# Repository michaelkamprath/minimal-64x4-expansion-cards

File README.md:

# Expansion Cards for Minimal 64x4 Computer
This repository contains various expansion cards for the [Minimal 64x4 Home Computer](https://github.com/slu4coder/Minimal-64x4-Home-Computer/) design by Carsten Herting, known as [slu4 on YouTube](https://www.youtube.com/channel/UCXYQcMpUBT3aaQKfmAVJNow).

## Back Plane
The [back plane provided in this repository](./expansion-backplane/) allows for more than one expansion card to be connected to the Minimal 64x4. It also provides a more convenient barrel jack power connector with a on/off switch to power the Minimal 64x4.

## Cards

* [**Speech Synthesizer**](./speech-synthesizer/) - This board provides support for interfacing with a TMS5220C speech synthesizer. 
* [**Multiplier Card**](./multiplier/) - This board provides a hardware implimentation of 8-bit integer multiplications, significantly improving the speed of multiplications over software-implementations.
* [**Timer**](./timer/) - Counts the cycles of the Minimal 64x4's system clock to enable precision timing of events.

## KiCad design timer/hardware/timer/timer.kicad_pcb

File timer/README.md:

# Timer - Clock Counter
This Timer card provides a convenient way to capture precise timing on the Minimal 64x4 by counting clock cycles. The counter is resettable to 0, allowing specific operations to be timed. The counter is 48 bits wide, which allows time ranges up to about 1.1 years at the Minimal 64x4's 8 MHz clock frequency.

## Hardware Design
[This card](./hardware/) uses six 74HC590 8-bit counters arranged in a cascading carry chain to create a 48-bit counter. The 74HC590 has tri-state outputs, so each counter IC is connected directly to the data bus and remains in high-Z unless selected to drive its latched value. Card control is handled by two 74HC688 comparators (address decode) and an ATF22V10C programmable logic device (control logic for read byte select, latch, and reset). The combinational logic is captured in [the PLD code](./pld-files/).

## Memory Map

Define:

`base = $FE00 + (x << 4) + y`

Where:
- `y` is controlled by jumper `J1` (address bit A3): `J1` open => `y = 0`, `J1` bridged => `y = 8`.
- `x` is controlled by jumpers `J2`-`J5` (address bits A4-A7): `J2` is A4 (LSB of `x`) and `J5` is A7 (MSB of `x`).
- Jumpers are named from the PCB silkscreen (`J1`-`J5`).

| Offset From `base` | R/W   | Function       | Description |
| ------------------ | ----- | -------------- | ----------- |
| `+0`               | Read  | Latched Byte 0 | Read latched counter value, byte 0 (LSB) |
| `+1`               | Read  | Latched Byte 1 | Read latched counter value, byte 1 |
| `+2`               | Read  | Latched Byte 2 | Read latched counter value, byte 2 |
| `+3`               | Read  | Latched Byte 3 | Read latched counter value, byte 3 |
| `+4`               | Read  | Latched Byte 4 | Read latched counter value, byte 4 |
| `+5`               | Read  | Latched Byte 5 | Read latched counter value, byte 5 (MSB) |
| `+6`               | Write | Latch Counter  | Latch (snapshot) the current 48-bit counter into the output registers. Any value may be written to trigger this action. |
| `+7`               | Write | Reset Counter  | Reset the counter value to `0`. Any value may be written to trigger this action. |

Concrete ranges for a selected `x`:
- `J1` open (`y = 0`): registers are at `$FEx0`-`$FEx7`.
- `J1` bridged (`y = 8`): registers are at `$FEx8`-`$FExF`.

Notes:
- Bridging all jumpers `J2` through `J5` sets `x` to `$F`; leaving them open sets `x` to `$0` (default).
- Reading `$FEx0`-`$FEx5` (or `$FEx8`-`$FExD` when `J1` is bridged) returns the last value latched by writing to the latch register, not necessarily the current counter value.
- Resetting the counter does not latch a `0` value.

### Default Jumper Setttings
The code in this repo assumes the timer card's base address is $FE28. This is accomplished by jumpering J1 and J3, and leaving the others open.

## Time Range
This card has a 48-bit counter that is read one byte at a time. Not all bytes need to be read, but reading fewer bytes reduces the effective time range captured. At the **Minimal 64x4**'s 8 MHz clock, the maximum time range by number of bytes read is shown in this table:

| Bytes | Bits | Max Seconds (s) | Approx Time                      |
| ----: | ---: | --------------: | -------------------------------- |
|     6 |   48 | 35184372.088832 | 407.22652996 days (~1.115 years) |
|     5 |   40 |   137438.953472 | 38.17748708 hours (~1.5907 days) |
|     4 |   32 |      536.870912 | 8.94784853 minutes               |
|     3 |   24 |        2.097152 | 2.097152 seconds                 |
|     2 |   16 |        0.008192 | 8.192 ms                         |
|     1 |    8 |        0.000032 | 32 µs                            |

The latched bytes are arranged in little-endian order: `base + 0` is the LSB and `base + 5` is the MSB.

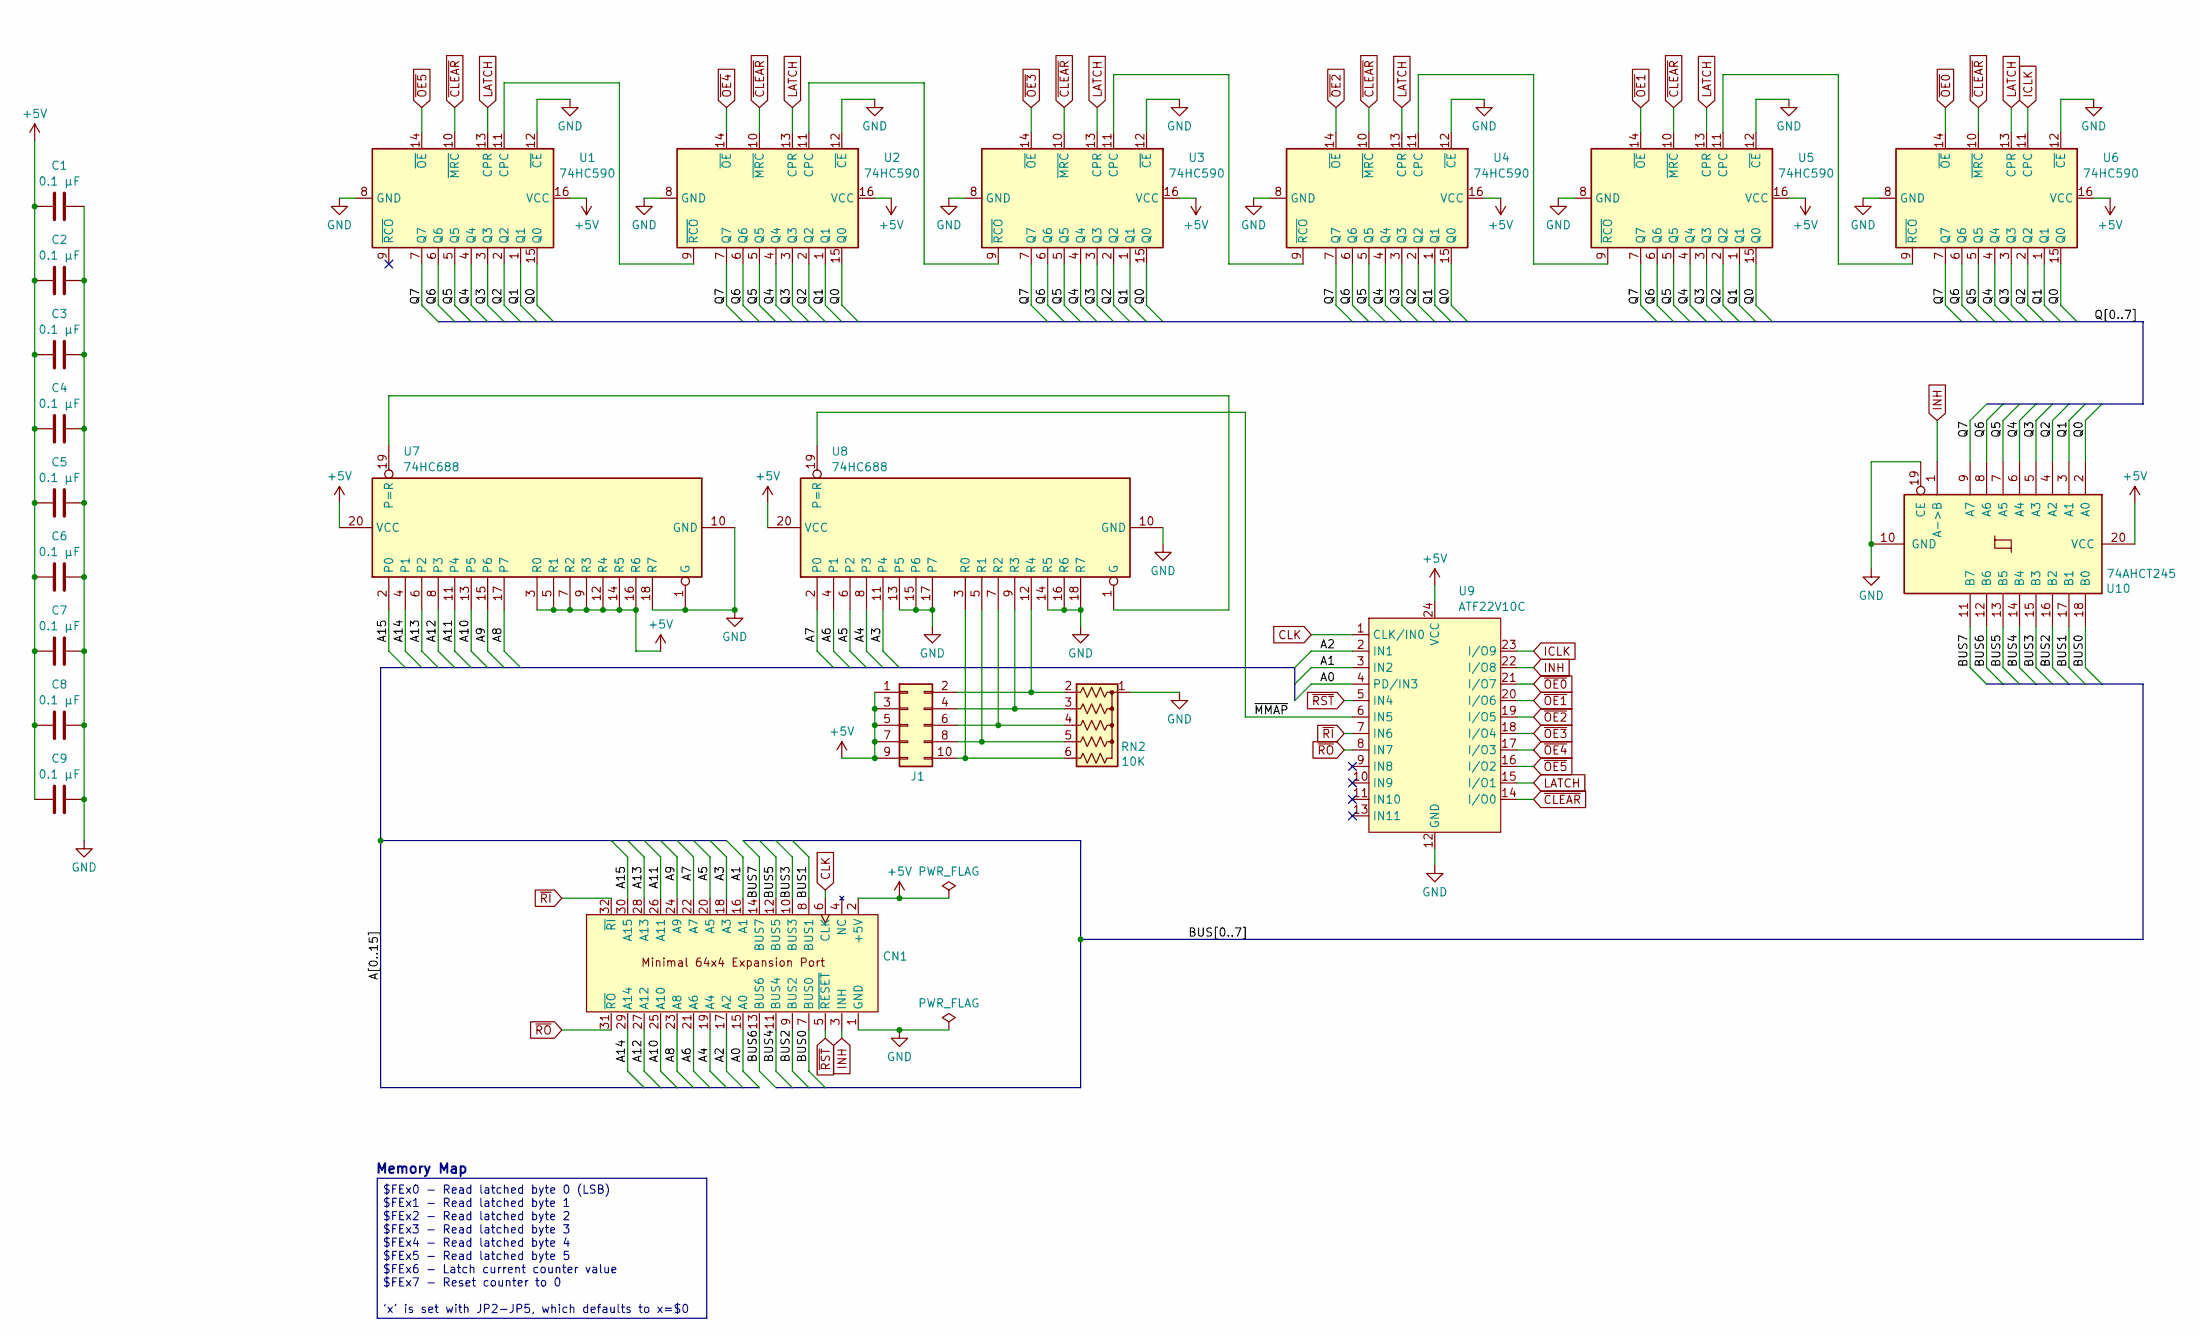
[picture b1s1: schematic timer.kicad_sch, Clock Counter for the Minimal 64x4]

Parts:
C1, C2, C3, C4, C5, C6, C7, C8, C9: 0.1 µF; C_Disc_D3.4mm_W2.1mm_P2.50mm
CN1: PinHeader_2x16_P2.54mm_Horizontal
J1: Conn_02x05_Odd_Even; PinHeader_2x05_P2.54mm_Vertical
RN2: 10K; R_Array_SIP6
U1, U2, U3, U4, U5, U6: 74HC590; DIP-16_W7.62mm_Socket
U7, U8: 74HC688; DIP-20_W7.62mm_Socket
U9: ATF22V10C; DIP-24_W7.62mm_Socket
U10: 74AHCT245; DIP-20_W7.62mm_Socket

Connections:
+5V: C1.1, C2.1, C3.1, C4.1, C5.1, C6.1, C7.1, C8.1, C9.1, CN1.2 (+5V), J1.1, J1.3, J1.5, J1.7, J1.9, U1.16 (VCC), U2.16 (VCC), U3.16 (VCC), U4.16 (VCC), U5.16 (VCC), U6.16 (VCC), U7.3 (R0), U7.5 (R1), U7.7 (R2), U7.9 (R3), U7.12 (R4), U7.14 (R5), U7.16 (R6), U7.20 (VCC), U8.20 (VCC), U9.24 (VCC), U10.20 (VCC)
/A0: CN1.15 (A0), U9.4 (PD/IN3)
/A1: CN1.16 (A1), U9.3 (IN2)
/A2: CN1.17 (A2), U9.2 (IN1)
/A3: CN1.18 (A3), U8.11 (P4)
/A4: CN1.19 (A4), U8.8 (P3)
/A5: CN1.20 (A5), U8.6 (P2)
/A6: CN1.21 (A6), U8.4 (P1)
/A7: CN1.22 (A7), U8.2 (P0)
/A8: CN1.23 (A8), U7.17 (P7)
/A9: CN1.24 (A9), U7.15 (P6)
/A10: CN1.25 (A10), U7.13 (P5)
/A11: CN1.26 (A11), U7.11 (P4)
/A12: CN1.27 (A12), U7.8 (P3)
/A13: CN1.28 (A13), U7.6 (P2)
/A14: CN1.29 (A14), U7.4 (P1)
/A15: CN1.30 (A15), U7.2 (P0)
/BUS0: CN1.7 (BUS0), U10.18 (B0)
/BUS1: CN1.8 (BUS1), U10.17 (B1)
/BUS2: CN1.9 (BUS2), U10.16 (B2)
/BUS3: CN1.10 (BUS3), U10.15 (B3)
/BUS4: CN1.11 (BUS4), U10.14 (B4)
/BUS5: CN1.12 (BUS5), U10.13 (B5)
/BUS6: CN1.13 (BUS6), U10.12 (B6)
/BUS7: CN1.14 (BUS7), U10.11 (B7)
/Q0: U1.15 (Q0), U2.15 (Q0), U3.15 (Q0), U4.15 (Q0), U5.15 (Q0), U6.15 (Q0), U10.2 (A0)
/Q1: U1.1 (Q1), U2.1 (Q1), U3.1 (Q1), U4.1 (Q1), U5.1 (Q1), U6.1 (Q1), U10.3 (A1)
/Q2: U1.2 (Q2), U2.2 (Q2), U3.2 (Q2), U4.2 (Q2), U5.2 (Q2), U6.2 (Q2), U10.4 (A2)
/Q3: U1.3 (Q3), U2.3 (Q3), U3.3 (Q3), U4.3 (Q3), U5.3 (Q3), U6.3 (Q3), U10.5 (A3)
/Q4: U1.4 (Q4), U2.4 (Q4), U3.4 (Q4), U4.4 (Q4), U5.4 (Q4), U6.4 (Q4), U10.6 (A4)
/Q5: U1.5 (Q5), U2.5 (Q5), U3.5 (Q5), U4.5 (Q5), U5.5 (Q5), U6.5 (Q5), U10.7 (A5)
/Q6: U1.6 (Q6), U2.6 (Q6), U3.6 (Q6), U4.6 (Q6), U5.6 (Q6), U6.6 (Q6), U10.8 (A6)
/Q7: U1.7 (Q7), U2.7 (Q7), U3.7 (Q7), U4.7 (Q7), U5.7 (Q7), U6.7 (Q7), U10.9 (A7)
/~MMAP: U8.19 (P=R), U9.6 (IN5)
CLK: CN1.6 (CLK), U9.1 (CLK/IN0)
GND: C1.2, C2.2, C3.2, C4.2, C5.2, C6.2, C7.2, C8.2, C9.2, CN1.1 (GND), RN2.1 (common), U1.8 (GND), U1.12 (~CE), U2.8 (GND), U2.12 (~CE), U3.8 (GND), U3.12 (~CE), U4.8 (GND), U4.12 (~CE), U5.8 (GND), U5.12 (~CE), U6.8 (GND), U6.12 (~CE), U7.1 (G), U7.10 (GND), U7.18 (R7), U8.10 (GND), U8.13 (P5), U8.14 (R5), U8.15 (P6), U8.16 (R6), U8.17 (P7), U8.18 (R7), U9.12 (GND), U10.10 (GND), U10.19 (CE)
ICLK: U6.11 (CPC), U9.23 (I/O9)
INH: CN1.3 (INH), U9.22 (I/O8), U10.1 (A->B)
LATCH: U1.13 (CPR), U2.13 (CPR), U3.13 (CPR), U4.13 (CPR), U5.13 (CPR), U6.13 (CPR), U9.15 (I/O1)
unnamed: J1.2, RN2.2 (R1), U8.12 (R4)
unnamed: J1.4, RN2.3 (R2), U8.9 (R3)
unnamed: J1.6, RN2.4 (R3), U8.7 (R2)
unnamed: J1.8, RN2.5 (R4), U8.5 (R1)
unnamed: J1.10, RN2.6 (R5), U8.3 (R0)
unnamed: U1.11 (CPC), U2.9 (~RCO)
unnamed: U2.11 (CPC), U3.9 (~RCO)
unnamed: U3.11 (CPC), U4.9 (~RCO)
unnamed: U4.11 (CPC), U5.9 (~RCO)
unnamed: U5.11 (CPC), U6.9 (~RCO)
unnamed: U7.19 (P=R), U8.1 (G)
~CLEAR: U1.10 (~MRC), U2.10 (~MRC), U3.10 (~MRC), U4.10 (~MRC), U5.10 (~MRC), U6.10 (~MRC), U9.14 (I/O0)
~OE0: U6.14 (~OE), U9.21 (I/O7)
~OE1: U5.14 (~OE), U9.20 (I/O6)
~OE2: U4.14 (~OE), U9.19 (I/O5)
~OE3: U3.14 (~OE), U9.18 (I/O4)
~OE4: U2.14 (~OE), U9.17 (I/O3)
~OE5: U1.14 (~OE), U9.16 (I/O2)
~RI: CN1.32 (~RI), U9.7 (IN6)
~RO: CN1.31 (~RO), U9.8 (IN7)
~RST: CN1.5 (~RESET), U9.5 (IN4)

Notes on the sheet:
$FEx0 - Read latched byte 0 (LSB) $FEx1 - Read latched byte 1 $FEx2 - Read latched byte 2 $FEx3 - Read latched byte 3 $FEx4 - Read latched byte 4 $FEx5 - Read latched byte 5 $FEx6 - Latch current counter value $FEx7 - Reset counter to 0 'x' is set with JP2-JP5, which defaults to x=$0
Memory Map

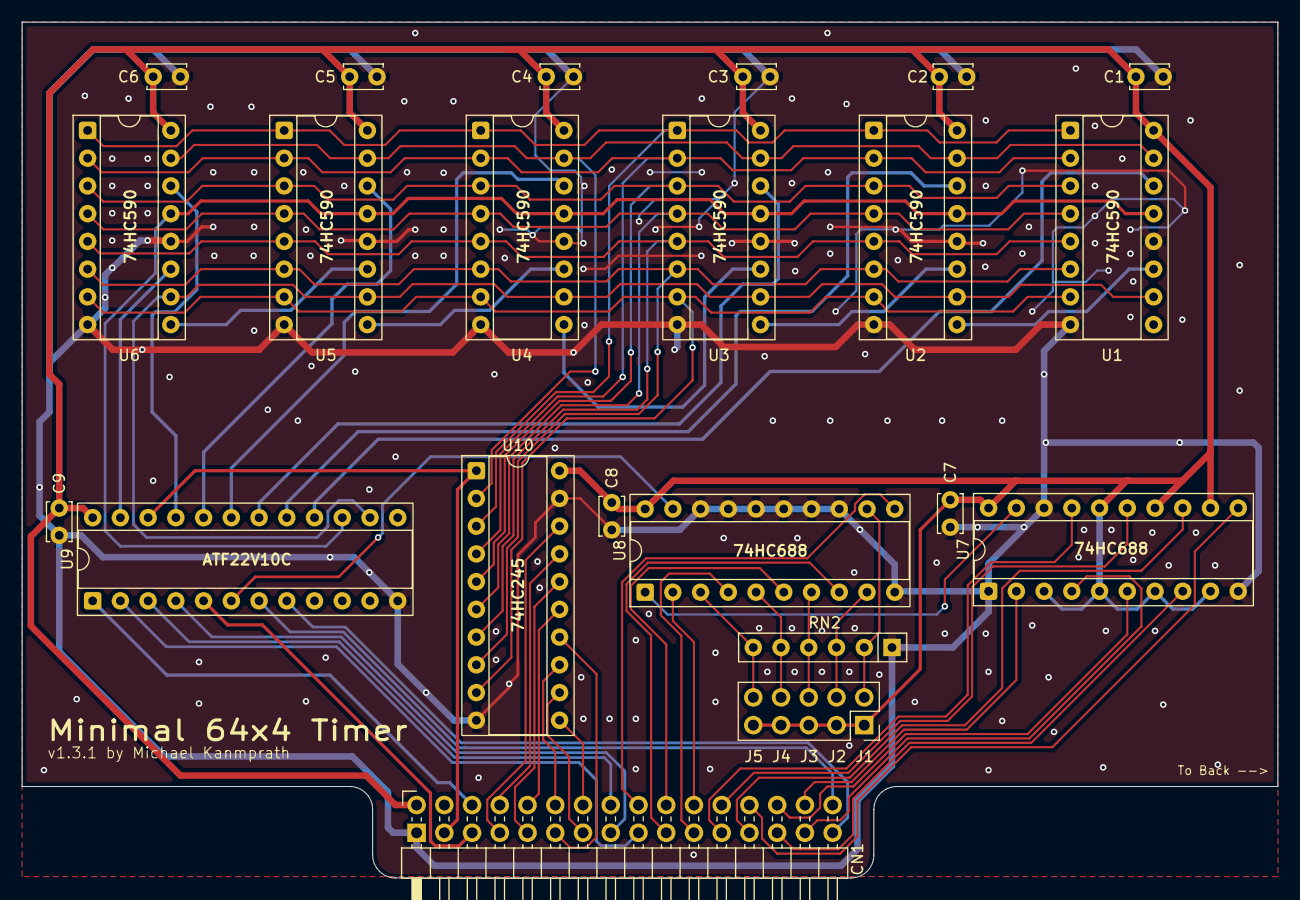
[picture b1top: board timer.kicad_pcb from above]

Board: 2 copper layers, 115.0 x 78.4 mm, 22 parts (0 on the bottom side), 60 nets.

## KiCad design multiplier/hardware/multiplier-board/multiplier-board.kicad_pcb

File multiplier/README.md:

# Integer Multiplication Accelerator for the Minimal 64x4 Computer
This project enables hardware-accelerated multiplication on the [Minimal 64x4 Home Computer](https://github.com/slu4coder/Minimal-64x4-Home-Computer/), exploring how multiplication works at a fundamental level in both software and hardware, using the Minimal 64x4 homebrew computer as a real-world test platform. Starting with a classic shifted-add multiplication algorithm implemented entirely in assembly, the project demonstrates both the mechanics and performance limits of software-based multiplication on an 8-bit CPU.

To dramatically improve performance, a dedicated hardware multiplier card is designed and built using discrete 74-series logic. The board implements a fully combinational 8-bit × 8-bit multiplier with memory-mapped I/O, allowing the CPU to offload multiplication and receive a 16-bit result in just a few clock cycles. The design is then extended in software to support full 16-bit × 16-bit multiplication through careful carry management.

The impact of hardware acceleration is demonstrated using a Mandelbrot renderer, where thousands of multiplications per frame make performance differences immediately visible. By comparing software-only and hardware-accelerated runs on real hardware, the project shows how a simple, purpose-built coprocessor can transform computational performance on a retro-style system.

# Hardware Multiplier Design
The hardware multiplier is a memory-mapped expansion board for the Minimal 64x4 that implements an 8-bit × 8-bit unsigned multiplication entirely in combinational logic. The design uses a planar array of 74AHCT08 AND gates to generate all partial products, followed by a cascade of 74HCT283 4-bit adders to sum those partial products and propagate carries. Because the multiplier core is purely combinational, no clocking, state machine, or control logic is required; once valid operands are presented, the result settles after the inherent gate propagation delay.

Operands are latched from the system data bus using 74AHCT374 registers to isolate the combinational logic from the shared bus and to ensure stable inputs during computation. The 16-bit result is continuously driven internally and presented to the host system through 74AHCT245 bidirectional bus transceivers when the board is selected. Address decoding is handled using 74HCT688 magnitude comparators, with a small programmable logic device (ATF16V8) providing glue logic for timing, output enable control, and bus arbitration.

Worst-case propagation delay is dominated by carry propagation through the adder array and is approximately 160 ns, corresponding to roughly two CPU cycles on an 8 MHz Minimal 64x4. From the CPU’s perspective, multiplication is reduced to a small number of memory writes and reads, enabling a substantial performance improvement over the software-only shifted-add implementation.

```text
                     ┌─────────────────────────┐
                     │        CPU / BUS        │
                     │  Address • Data • Ctrl  │
                     └───────────┬─────────────┘
                                 │
                        Memory-Mapped I/O
                                 │
        ┌────────────────────────▼────────────────────────┐
        │            Hardware Multiplier Board            │
        │                                                 │
        │  ┌───────────────┐      ┌────────────────────┐  │
        │  │ Input Latch A │◄─────┤                    │  │
        │  │  (8-bit)      │      │                    │  │
        │  └───────────────┘      │                    │  │
        │                         │                    │  │
        │  ┌───────────────┐      │  Combinational     │  │
        │  │ Input Latch B │◄─────┤  Multiplier Core   │  │
        │  │  (8-bit)      │      │  (AND Plane +      │  │
        │  └───────────────┘      │   Adder Array)     │  │
        │                         │                    │  │
        │                         │                    │  │
        │                         └─────────┬──────────┘  │
        │                                   │             │
        │                          16-bit Result          │
        │                                   │             │
        │                    ┌──────────────▼────────────┐│
        │                    │  Output Bus Transceivers  ││
        │                    │       (16-bit)            ││
        │                    └──────────────┬────────────┘│
        │                                   │             │
        │  ┌──────────────────────────┐     │             │
        │  │ Address Decode & Control │◄────┘             │
        │  │ (Comparators + PLD)      │                   │
        │  └──────────────────────────┘                   │
        └─────────────────────────────────────────────────┘
```
The overall structure of the hardware multiplier is shown in the block diagram above. The board interfaces with the CPU exclusively through memory-mapped I/O on the shared system bus. Operand values are written by the CPU into two 8-bit input latches (Operand A and Operand B), which isolate the multiplier core from bus activity and continuously present stable inputs to the combinational logic.

At the center of the design is a purely combinational multiplier core composed of an AND-gate partial-product plane followed by an adder array that collapses those partial products into a 16-bit result. Because the core has no internal state, clocking, or control signals, the result is produced automatically as signals propagate through the logic once the operands are latched.

The 16-bit result is connected to the system data bus through output bus transceivers that are enabled only during valid read cycles. Address decoding and timing control logic ensure the board responds only within its assigned address range and never drives the bus outside of those cycles. From the CPU’s perspective, the hardware multiplier appears as a small set of deterministic, memory-mapped registers, with computation latency bounded solely by combinational propagation delay.

# Compiling the Software
All software found in the [software](./software/) directory is compiled with [BespokeASM](https://github.com/michaelkamprath/bespokeasm), which supports the Minimal 64x4. [Carsten Herting](https://github.com/slu4coder), the creator of the Minimal 64x4, also provides an assembler for it, but that assembler is quite minimal (by design). One key shortcoming is the inability to import library code into the current compilation. BespokeASM enables importing libraries and includes several other features that this project’s software depends on.

To compile the speech code in this repository, use the following command:

```sh
bespokeasm compile -c /path/to/bespokeasm/examples/slu4-minimal-64x4/slu4-minimal-64x4.yaml -n -p -t intel_hex -D USE_ACCELERATOR mandelbrot.min64x4
```
Where `/path/to/bespokeasm` is the path to the BespokeASM repository on your computer. You may remove the `-D USE_ACCELERATOR` if you wish to compile the program to use software-only multiplication.

This will produce an Intel HEX representation of the compiled program, which can then be sent to the Minimal 64x4 using its `receive` command.

# Video

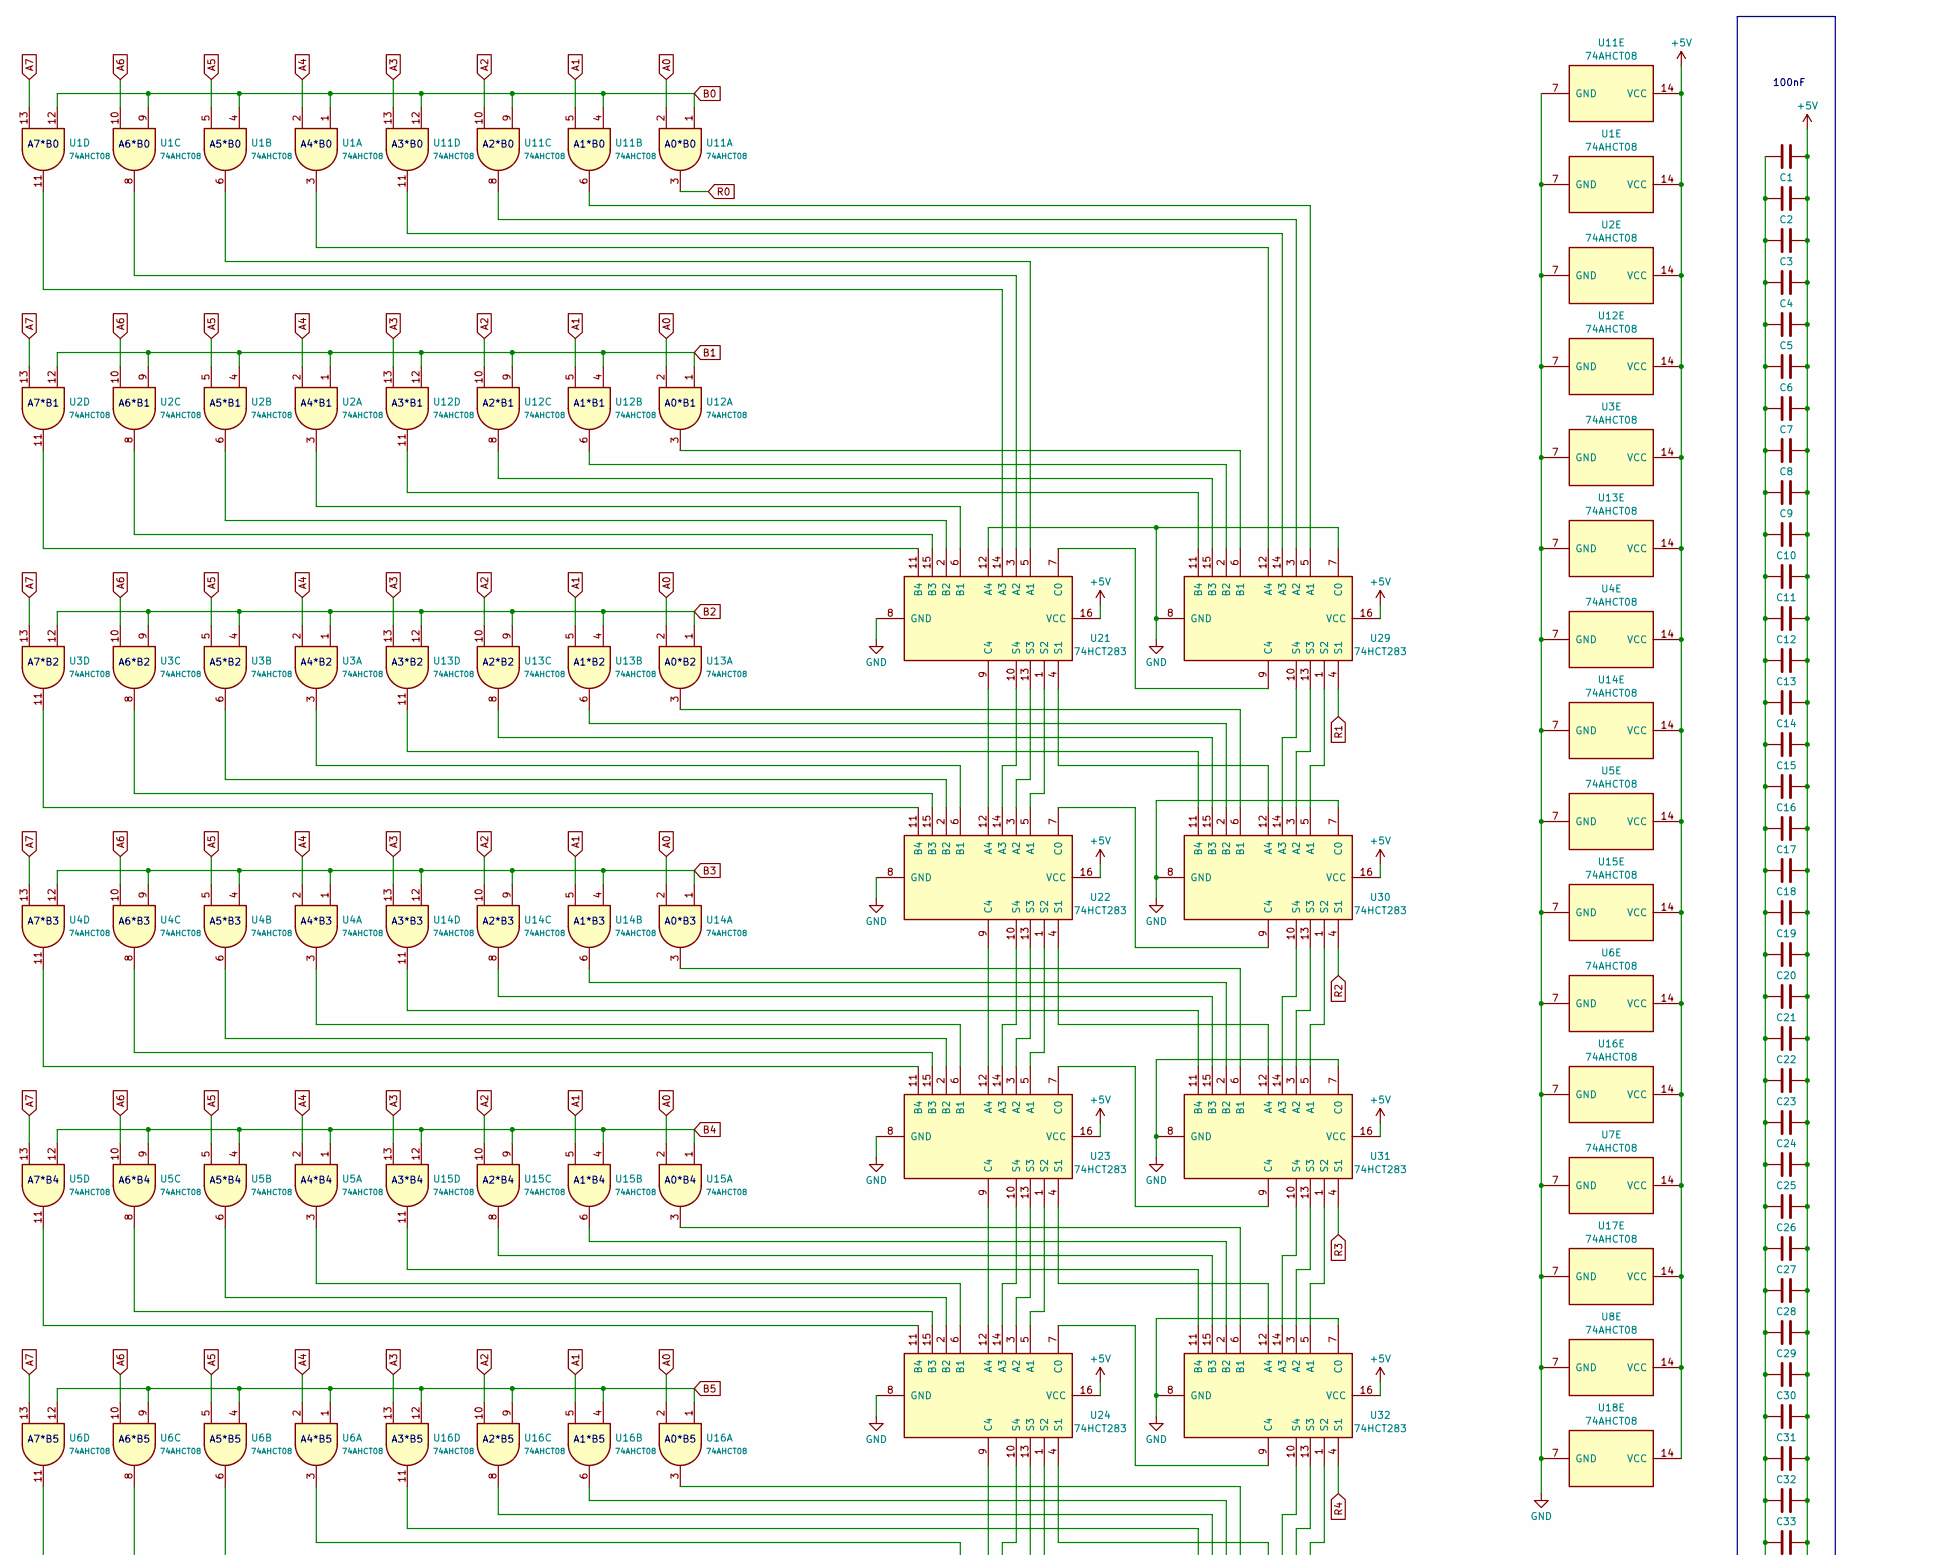
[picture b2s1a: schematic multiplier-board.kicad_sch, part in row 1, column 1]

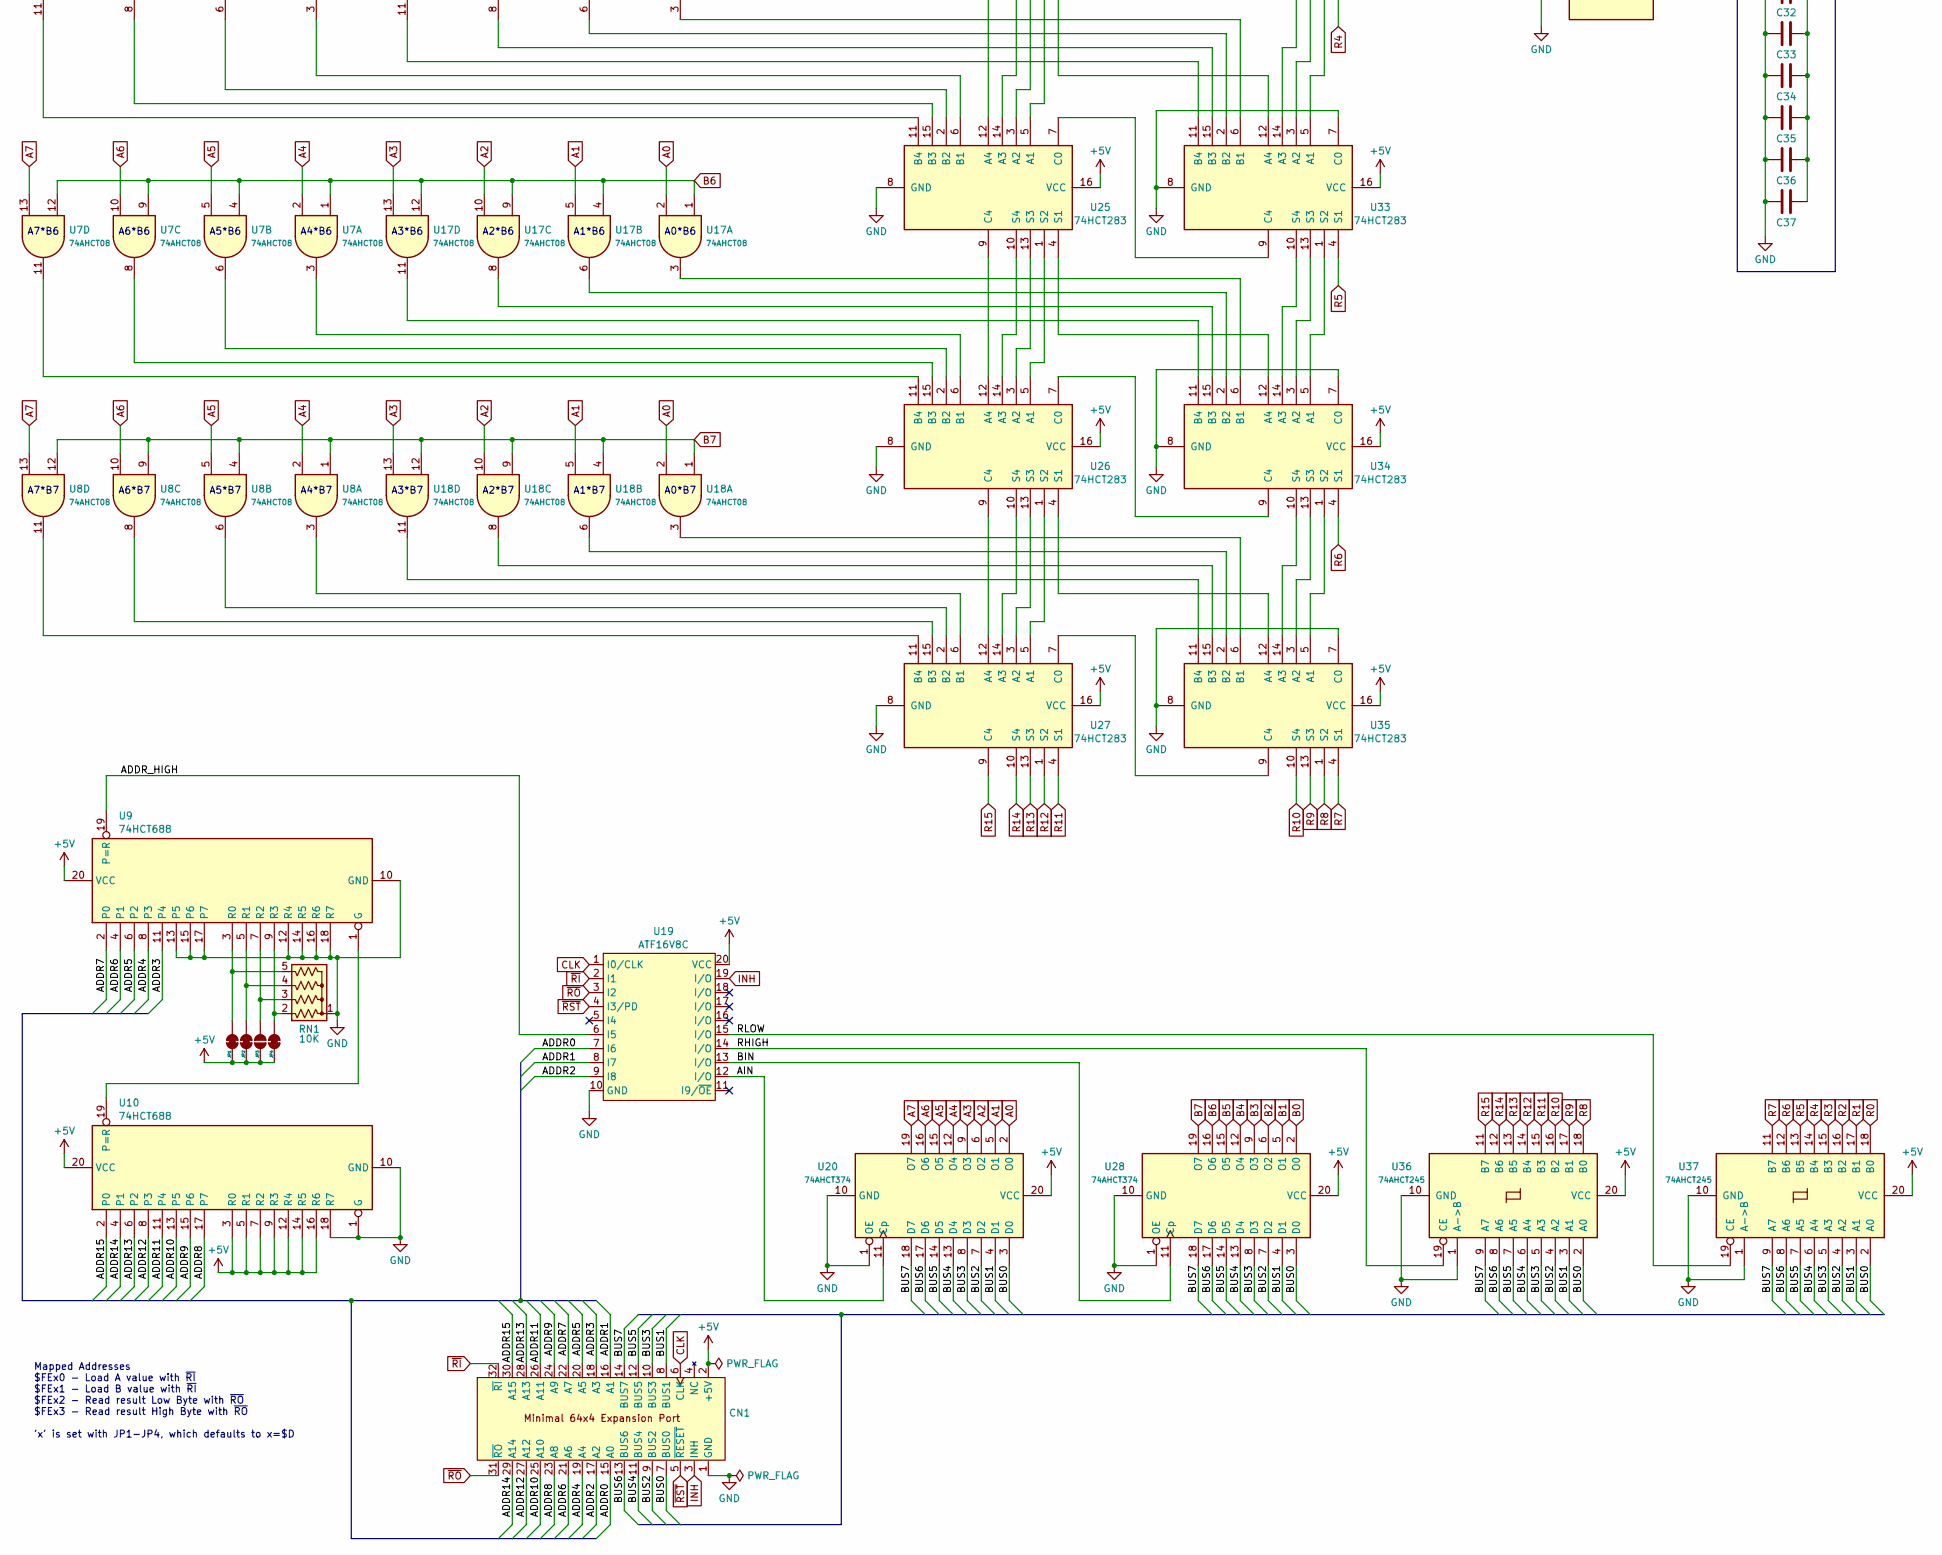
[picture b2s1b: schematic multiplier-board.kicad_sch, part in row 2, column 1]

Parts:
C1, C2, C3, C4, C5, C6, C7, C8, C9, C10, C11, C12, C13, C14, C15, C16, C17, C18, C19, C20, C21, C22, C23, C24, C25, C26, C27, C28, C29, C30, C31, C32, C33, C34, C35, C36, C37: 100 nF; C_0805_2012Metric_Pad1.18x1.45mm_HandSolder
CN1: PinHeader_2x16_P2.54mm_Horizontal
JP1, JP2, JP4: SolderJumper_2_Bridged; SolderJumper-2_P1.3mm_Bridged_RoundedPad1.0x1.5mm
JP3: SolderJumper_2_Open; SolderJumper-2_P1.3mm_Open_RoundedPad1.0x1.5mm
RN1: 10K; R_Array_SIP5
U1, U2, U3, U4, U5, U6, U7, U8, U11, U12, U13, U14, U15, U16, U17, U18: 74AHCT08; SOIC-14_3.9x8.7mm_P1.27mm
U9, U10: 74HCT688; SOIC-20W_7.5x12.8mm_P1.27mm
U19: ATF16V8C; DIP-20_W7.62mm_Socket
U20, U28: 74AHCT374; SOIC-20W_7.5x12.8mm_P1.27mm
U21, U22, U23, U24, U25, U26, U27, U29, U30, U31, U32, U33, U34, U35: 74HCT283; SOIC-16_3.9x9.9mm_P1.27mm
U36, U37: 74AHCT245; SOIC-20W_7.5x12.8mm_P1.27mm

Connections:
+5V: C1.2, C2.2, C3.2, C4.2, C5.2, C6.2, C7.2, C8.2, C9.2, C10.2, C11.2, C12.2, C13.2, C14.2, C15.2, C16.2, C17.2, C18.2, C19.2, C20.2, C21.2, C22.2, C23.2, C24.2, C25.2, C26.2, C27.2, C28.2, C29.2, C30.2, C31.2, C32.2, C33.2, C34.2, C35.2, C36.2, C37.2, CN1.2 (+5V), JP1.1 (A), JP2.1 (A), JP3.1 (A), JP4.1 (A), U1.14 (VCC), U2.14 (VCC), U3.14 (VCC), U4.14 (VCC), U5.14 (VCC), U6.14 (VCC), U7.14 (VCC), U8.14 (VCC), U9.20 (VCC), U10.3 (R0), U10.5 (R1), U10.7 (R2), U10.9 (R3), U10.12 (R4), U10.14 (R5), U10.16 (R6), U10.20 (VCC), U11.14 (VCC), U12.14 (VCC), U13.14 (VCC), U14.14 (VCC), U15.14 (VCC), U16.14 (VCC), U17.14 (VCC), U18.14 (VCC), U19.20 (VCC), U20.20 (VCC), U21.16 (VCC), U22.16 (VCC), U23.16 (VCC), U24.16 (VCC), U25.16 (VCC), U26.16 (VCC), U27.16 (VCC), U28.20 (VCC), U29.16 (VCC), U30.16 (VCC), U31.16 (VCC), U32.16 (VCC), U33.16 (VCC), U34.16 (VCC), U35.16 (VCC), U36.20 (VCC), U37.20 (VCC)
/ADDR0: CN1.15 (A0), U19.7 (I6)
/ADDR1: CN1.16 (A1), U19.8 (I7)
/ADDR2: CN1.17 (A2), U19.9 (I8)
/ADDR3: CN1.18 (A3), U9.11 (P4)
/ADDR4: CN1.19 (A4), U9.8 (P3)
/ADDR5: CN1.20 (A5), U9.6 (P2)
/ADDR6: CN1.21 (A6), U9.4 (P1)
/ADDR7: CN1.22 (A7), U9.2 (P0)
/ADDR8: CN1.23 (A8), U10.17 (P7)
/ADDR9: CN1.24 (A9), U10.15 (P6)
/ADDR10: CN1.25 (A10), U10.13 (P5)
/ADDR11: CN1.26 (A11), U10.11 (P4)
/ADDR12: CN1.27 (A12), U10.8 (P3)
/ADDR13: CN1.28 (A13), U10.6 (P2)
/ADDR14: CN1.29 (A14), U10.4 (P1)
/ADDR15: CN1.30 (A15), U10.2 (P0)
/ADDR_HIGH: U9.19 (P=R), U19.6 (I5)
/AIN: U19.12 (I/O), U20.11 (Cp)
/BIN: U19.13 (I/O), U28.11 (Cp)
/BUS0: CN1.7 (BUS0), U20.3 (D0), U28.3 (D0), U36.2 (A0), U37.2 (A0)
/BUS1: CN1.8 (BUS1), U20.4 (D1), U28.4 (D1), U36.3 (A1), U37.3 (A1)
/BUS2: CN1.9 (BUS2), U20.7 (D2), U28.7 (D2), U36.4 (A2), U37.4 (A2)
/BUS3: CN1.10 (BUS3), U20.8 (D3), U28.8 (D3), U36.5 (A3), U37.5 (A3)
/BUS4: CN1.11 (BUS4), U20.13 (D4), U28.13 (D4), U36.6 (A4), U37.6 (A4)
/BUS5: CN1.12 (BUS5), U20.14 (D5), U28.14 (D5), U36.7 (A5), U37.7 (A5)
/BUS6: CN1.13 (BUS6), U20.17 (D6), U28.17 (D6), U36.8 (A6), U37.8 (A6)
/BUS7: CN1.14 (BUS7), U20.18 (D7), U28.18 (D7), U36.9 (A7), U37.9 (A7)
/RHIGH: U19.14 (I/O), U36.19 (CE)
/RLOW: U19.15 (I/O), U37.19 (CE)
A0: U11.2, U12.2, U13.2, U14.2, U15.2, U16.2, U17.2, U18.2, U20.2 (O0)
A1: U11.5, U12.5, U13.5, U14.5, U15.5, U16.5, U17.5, U18.5, U20.5 (O1)
A2: U11.10, U12.10, U13.10, U14.10, U15.10, U16.10, U17.10, U18.10, U20.6 (O2)
A3: U11.13, U12.13, U13.13, U14.13, U15.13, U16.13, U17.13, U18.13, U20.9 (O3)
A4: U1.2, U2.2, U3.2, U4.2, U5.2, U6.2, U7.2, U8.2, U20.12 (O4)
A5: U1.5, U2.5, U3.5, U4.5, U5.5, U6.5, U7.5, U8.5, U20.15 (O5)
A6: U1.10, U2.10, U3.10, U4.10, U5.10, U6.10, U7.10, U8.10, U20.16 (O6)
A7: U1.13, U2.13, U3.13, U4.13, U5.13, U6.13, U7.13, U8.13, U20.19 (O7)
B0: U1.1, U1.4, U1.9, U1.12, U11.1, U11.4, U11.9, U11.12, U28.2 (O0)
B1: U2.1, U2.4, U2.9, U2.12, U12.1, U12.4, U12.9, U12.12, U28.5 (O1)
B2: U3.1, U3.4, U3.9, U3.12, U13.1, U13.4, U13.9, U13.12, U28.6 (O2)
B3: U4.1, U4.4, U4.9, U4.12, U14.1, U14.4, U14.9, U14.12, U28.9 (O3)
B4: U5.1, U5.4, U5.9, U5.12, U15.1, U15.4, U15.9, U15.12, U28.12 (O4)
B5: U6.1, U6.4, U6.9, U6.12, U16.1, U16.4, U16.9, U16.12, U28.15 (O5)
B6: U7.1, U7.4, U7.9, U7.12, U17.1, U17.4, U17.9, U17.12, U28.16 (O6)
B7: U8.1, U8.4, U8.9, U8.12, U18.1, U18.4, U18.9, U18.12, U28.19 (O7)
CLK: CN1.6 (CLK), U19.1 (I0/CLK)
GND: C1.1, C2.1, C3.1, C4.1, C5.1, C6.1, C7.1, C8.1, C9.1, C10.1, C11.1, C12.1, C13.1, C14.1, C15.1, C16.1, C17.1, C18.1, C19.1, C20.1, C21.1, C22.1, C23.1, C24.1, C25.1, C26.1, C27.1, C28.1, C29.1, C30.1, C31.1, C32.1, C33.1, C34.1, C35.1, C36.1, C37.1, CN1.1 (GND), RN1.1 (common), U1.7 (GND), U2.7 (GND), U3.7 (GND), U4.7 (GND), U5.7 (GND), U6.7 (GND), U7.7 (GND), U8.7 (GND), U9.10 (GND), U9.12 (R4), U9.13 (P5), U9.14 (R5), U9.15 (P6), U9.16 (R6), U9.17 (P7), U9.18 (R7), U10.1 (G), U10.10 (GND), U10.18 (R7), U11.7 (GND), U12.7 (GND), U13.7 (GND), U14.7 (GND), U15.7 (GND), U16.7 (GND), U17.7 (GND), U18.7 (GND), U19.10 (GND), U20.1 (OE), U20.10 (GND), U21.8 (GND), U21.12 (A4), U22.8 (GND), U23.8 (GND), U24.8 (GND), U25.8 (GND), U26.8 (GND), U27.8 (GND), U28.1 (OE), U28.10 (GND), U29.7 (C0), U29.8 (GND), U30.7 (C0), U30.8 (GND), U31.7 (C0), U31.8 (GND), U32.7 (C0), U32.8 (GND), U33.7 (C0), U33.8 (GND), U34.7 (C0), U34.8 (GND), U35.7 (C0), U35.8 (GND), U36.1 (A->B), U36.10 (GND), U37.1 (A->B), U37.10 (GND)
INH: CN1.3 (INH), U19.19 (I/O)
unnamed: JP1.2 (B), RN1.5 (R4), U9.3 (R0)
unnamed: JP2.2 (B), RN1.4 (R3), U9.5 (R1)
unnamed: JP3.2 (B), RN1.3 (R2), U9.7 (R2)
unnamed: JP4.2 (B), RN1.2 (R1), U9.9 (R3)
unnamed: U9.1 (G), U10.19 (P=R)
unnamed: U1.6, U21.5 (A1)
unnamed: U1.8, U21.3 (A2)
unnamed: U1.11, U21.14 (A3)
unnamed: U2.3, U21.6 (B1)
unnamed: U2.6, U21.2 (B2)
unnamed: U2.8, U21.15 (B3)
unnamed: U2.11, U21.11 (B4)
unnamed: U21.7 (C0), U29.9 (C4)
unnamed: U21.9 (C4), U22.12 (A4)
unnamed: U21.4 (S1), U30.12 (A4)
unnamed: U21.1 (S2), U22.5 (A1)
unnamed: U21.13 (S3), U22.3 (A2)
unnamed: U21.10 (S4), U22.14 (A3)
unnamed: U3.3, U22.6 (B1)
unnamed: U3.6, U22.2 (B2)
unnamed: U3.8, U22.15 (B3)
unnamed: U3.11, U22.11 (B4)
unnamed: U22.7 (C0), U30.9 (C4)
unnamed: U22.9 (C4), U23.12 (A4)
unnamed: U22.4 (S1), U31.12 (A4)
unnamed: U22.1 (S2), U23.5 (A1)
unnamed: U22.13 (S3), U23.3 (A2)
unnamed: U22.10 (S4), U23.14 (A3)
unnamed: U4.3, U23.6 (B1)
unnamed: U4.6, U23.2 (B2)
unnamed: U4.8, U23.15 (B3)
unnamed: U4.11, U23.11 (B4)
unnamed: U23.7 (C0), U31.9 (C4)
unnamed: U23.9 (C4), U24.12 (A4)
unnamed: U23.4 (S1), U32.12 (A4)
unnamed: U23.1 (S2), U24.5 (A1)
unnamed: U23.13 (S3), U24.3 (A2)
unnamed: U23.10 (S4), U24.14 (A3)
unnamed: U5.3, U24.6 (B1)
unnamed: U5.6, U24.2 (B2)
unnamed: U5.8, U24.15 (B3)
unnamed: U5.11, U24.11 (B4)
unnamed: U24.7 (C0), U32.9 (C4)
unnamed: U24.9 (C4), U25.12 (A4)
unnamed: U24.4 (S1), U33.12 (A4)
unnamed: U24.1 (S2), U25.5 (A1)
unnamed: U24.13 (S3), U25.3 (A2)
unnamed: U24.10 (S4), U25.14 (A3)
unnamed: U6.3, U25.6 (B1)
unnamed: U6.6, U25.2 (B2)
unnamed: U6.8, U25.15 (B3)
unnamed: U6.11, U25.11 (B4)
unnamed: U25.7 (C0), U33.9 (C4)
unnamed: U25.9 (C4), U26.12 (A4)
unnamed: U25.4 (S1), U34.12 (A4)
unnamed: U25.1 (S2), U26.5 (A1)
unnamed: U25.13 (S3), U26.3 (A2)
unnamed: U25.10 (S4), U26.14 (A3)
unnamed: U7.3, U26.6 (B1)
unnamed: U7.6, U26.2 (B2)
unnamed: U7.8, U26.15 (B3)
unnamed: U7.11, U26.11 (B4)
unnamed: U26.7 (C0), U34.9 (C4)
unnamed: U26.9 (C4), U27.12 (A4)
unnamed: U26.4 (S1), U35.12 (A4)
unnamed: U26.1 (S2), U27.5 (A1)
unnamed: U26.13 (S3), U27.3 (A2)
unnamed: U26.10 (S4), U27.14 (A3)
unnamed: U8.3, U27.6 (B1)
unnamed: U8.6, U27.2 (B2)
unnamed: U8.8, U27.15 (B3)
unnamed: U8.11, U27.11 (B4)
unnamed: U27.7 (C0), U35.9 (C4)
unnamed: U11.6, U29.5 (A1)
unnamed: U11.8, U29.3 (A2)
unnamed: U11.11, U29.14 (A3)
unnamed: U1.3, U29.12 (A4)
unnamed: U12.3, U29.6 (B1)
unnamed: U12.6, U29.2 (B2)
unnamed: U12.8, U29.15 (B3)
unnamed: U12.11, U29.11 (B4)
unnamed: U29.1 (S2), U30.5 (A1)
unnamed: U29.13 (S3), U30.3 (A2)
unnamed: U29.10 (S4), U30.14 (A3)
unnamed: U13.3, U30.6 (B1)
unnamed: U13.6, U30.2 (B2)
unnamed: U13.8, U30.15 (B3)
unnamed: U13.11, U30.11 (B4)
unnamed: U30.1 (S2), U31.5 (A1)
unnamed: U30.13 (S3), U31.3 (A2)
unnamed: U30.10 (S4), U31.14 (A3)
unnamed: U14.3, U31.6 (B1)
unnamed: U14.6, U31.2 (B2)
unnamed: U14.8, U31.15 (B3)
unnamed: U14.11, U31.11 (B4)
unnamed: U31.1 (S2), U32.5 (A1)
unnamed: U31.13 (S3), U32.3 (A2)
unnamed: U31.10 (S4), U32.14 (A3)
unnamed: U15.3, U32.6 (B1)
unnamed: U15.6, U32.2 (B2)
unnamed: U15.8, U32.15 (B3)
unnamed: U15.11, U32.11 (B4)
unnamed: U32.1 (S2), U33.5 (A1)
unnamed: U32.13 (S3), U33.3 (A2)
unnamed: U32.10 (S4), U33.14 (A3)
unnamed: U16.3, U33.6 (B1)
unnamed: U16.6, U33.2 (B2)
unnamed: U16.8, U33.15 (B3)
unnamed: U16.11, U33.11 (B4)
unnamed: U33.1 (S2), U34.5 (A1)
unnamed: U33.13 (S3), U34.3 (A2)
unnamed: U33.10 (S4), U34.14 (A3)
unnamed: U17.3, U34.6 (B1)
unnamed: U17.6, U34.2 (B2)
unnamed: U17.8, U34.15 (B3)
unnamed: U17.11, U34.11 (B4)
unnamed: U34.1 (S2), U35.5 (A1)
unnamed: U34.13 (S3), U35.3 (A2)
unnamed: U34.10 (S4), U35.14 (A3)
unnamed: U18.3, U35.6 (B1)
unnamed: U18.6, U35.2 (B2)
unnamed: U18.8, U35.15 (B3)
unnamed: U18.11, U35.11 (B4)
R0: U11.3, U37.18 (B0)
R1: U29.4 (S1), U37.17 (B1)
R2: U30.4 (S1), U37.16 (B2)
R3: U31.4 (S1), U37.15 (B3)
R4: U32.4 (S1), U37.14 (B4)
R5: U33.4 (S1), U37.13 (B5)
R6: U34.4 (S1), U37.12 (B6)
R7: U35.4 (S1), U37.11 (B7)
R8: U35.1 (S2), U36.18 (B0)
R9: U35.13 (S3), U36.17 (B1)
R10: U35.10 (S4), U36.16 (B2)
R11: U27.4 (S1), U36.15 (B3)
R12: U27.1 (S2), U36.14 (B4)
R13: U27.13 (S3), U36.13 (B5)
R14: U27.10 (S4), U36.12 (B6)
R15: U27.9 (C4), U36.11 (B7)
~RI: CN1.32 (~RI), U19.2 (I1)
~RO: CN1.31 (~RO), U19.3 (I2)
~RST: CN1.5 (~RESET), U19.4 (I3/PD)

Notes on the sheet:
A5*B6
A6*B7
A5*B1
A2*B4
A1*B3
A1*B5
A2*B5
A1*B2
A3*B2
A2*B1
A2*B0
A2*B6
A4*B1
A4*B0
A0*B3
A6*B3
A4*B3
A7*B6
A0*B0
A2*B7
A5*B5
A7*B4
A7*B0
A4*B6
A6*B4
A3*B6
A3*B5
A7*B3
A2*B2
A4*B2
A1*B4
A3*B0
A5*B0
A5*B7
A1*B6
A0*B7
A4*B7
Mapped Addresses $FEx0 - Load A value with ~{RI} $FEx1 - Load B value with ~{RI} $FEx2 - Read result Low Byte with ~{RO} $FEx3 - Read result High Byte with ~{RO} 'x' is set with JP1-JP4, which defaults to x=$D
A0*B2
A6*B2
